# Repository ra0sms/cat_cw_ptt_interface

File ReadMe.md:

# CAT CW PTT AUDIO interface for a transceiver

More information - https://ra0sms.com/cat-cw-ptt-audio-interface/

------

------

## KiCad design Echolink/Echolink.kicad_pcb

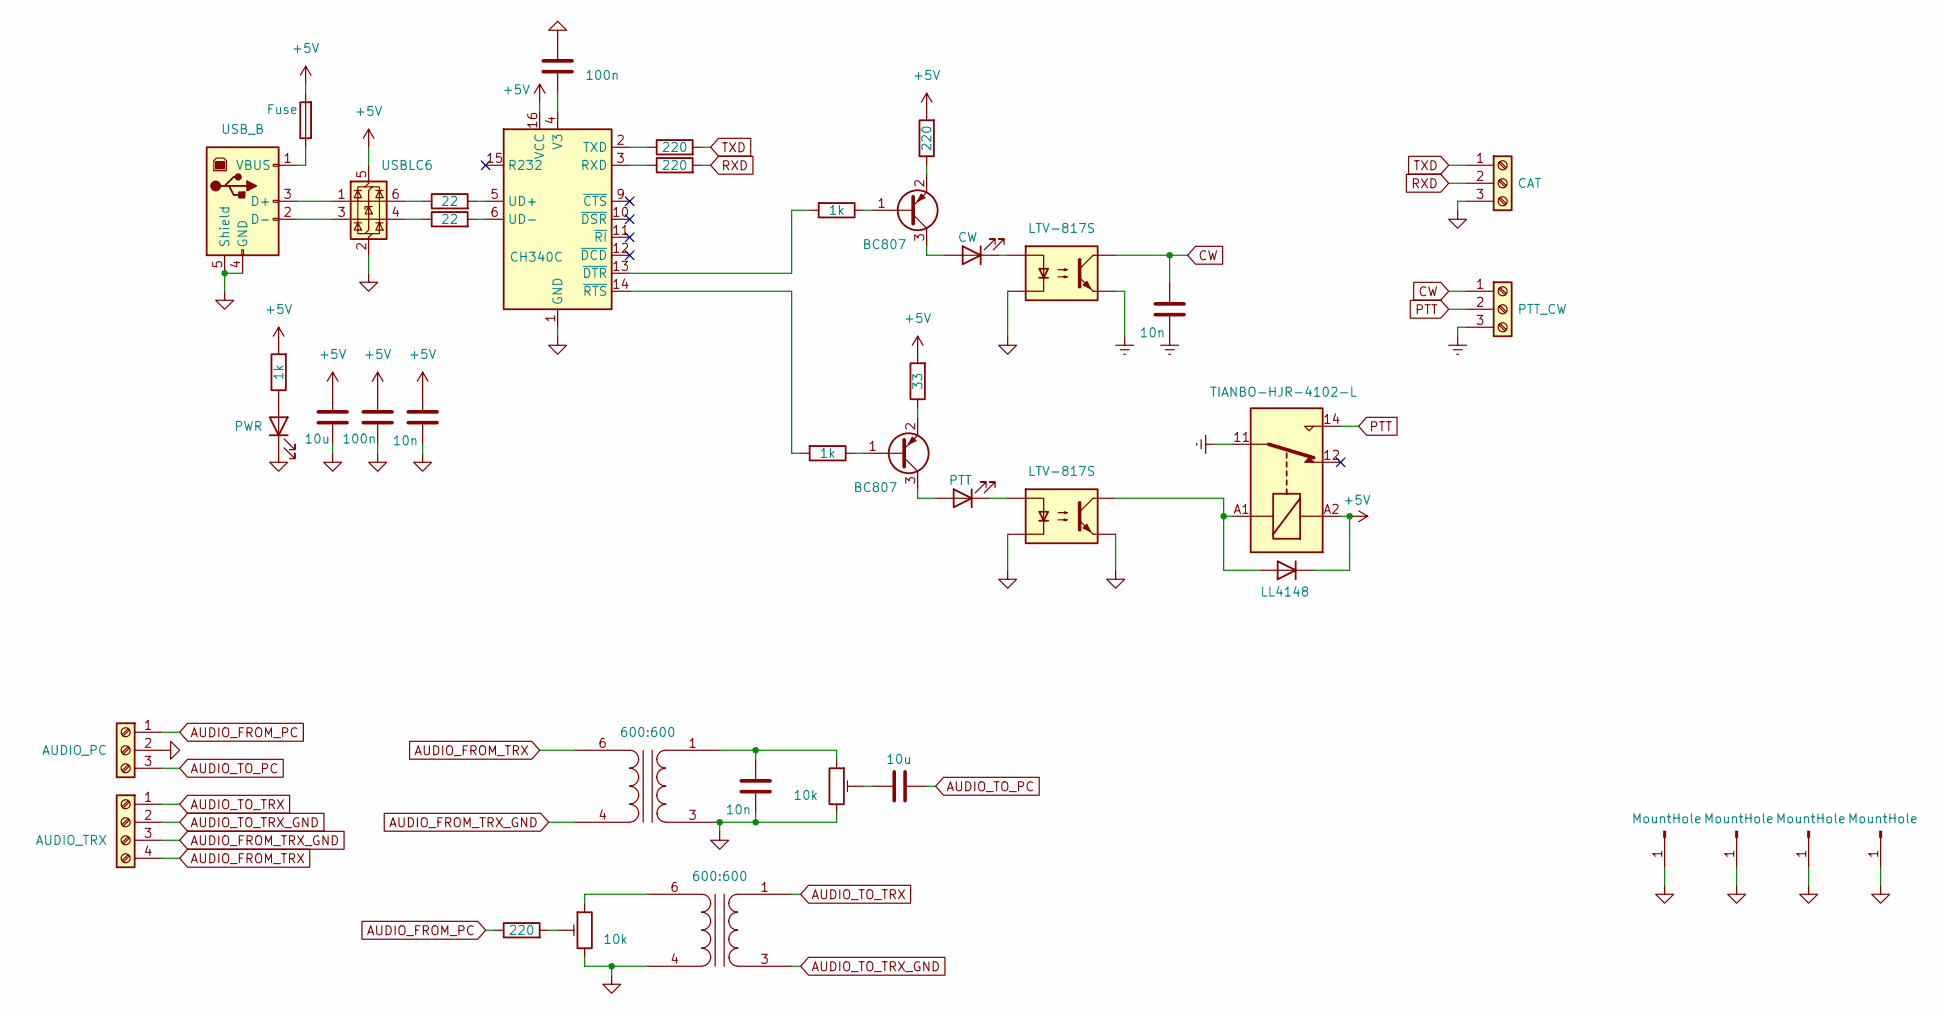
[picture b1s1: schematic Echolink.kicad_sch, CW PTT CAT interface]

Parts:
C1, C8: 10u; C_1206_3216Metric
C2, C3: 100n; C_1206_3216Metric
C4, C5, C7: 10n; C_1206_3216Metric
D1: PWR; LED_1206_3216Metric
D2: CW; LED_1206_3216Metric
D3: LL4148; D_MiniMELF
D4: PTT; LED_1206_3216Metric
F1: Fuse; R_1206_3216Metric
J1: USB_B; USB_B_OST_USB-B1HSxx_Horizontal
J2: AUDIO_PC; TerminalBlock_MetzConnect_Type055_RT01503HDWU_1x03_P5.00mm_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
J3: AUDIO_TRX; TerminalBlock_MetzConnect_Type055_RT01504HDWU_1x04_P5.00mm_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
J4, J7, J8, J9: MountHole; MountingHole_3.2mm_M3_DIN965_Pad
J5: CAT; TerminalBlock_MetzConnect_Type055_RT01503HDWU_1x03_P5.00mm_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
J6: PTT_CW; TerminalBlock_MetzConnect_Type055_RT01503HDWU_1x03_P5.00mm_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
K11: TIANBO-HJR-4102-L; Relay_SPDT_CUI_SR5
Q1, Q2: BC807; SOT-23
R1, R4, R7, R10: 220; R_1206_3216Metric
R2, R3: 22; R_1206_3216Metric
R5, R6, R8: 1k; R_1206_3216Metric
R9: 33; R_1206_3216Metric
RV1, RV2: 10k; Potentiometer_Bourns_3296W_Vertical
T1, T2: 600:600; Transformer_NF_ETAL_1-1_P1200
U1: CH340C; SOIC-16_3.9x9.9mm_P1.27mm
U2: USBLC6; SOT-23-6
U5, U6: LTV-817S; SMDIP-4_W9.53mm

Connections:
+5V: C1.1, C3.1, C4.1, D3.1 (K), F1.2, K11.A2, R5.2, R7.2, R9.2, U1.16 (VCC), U2.5 (VBUS)
AUDIO_FROM_PC: J2.1, R10.1
AUDIO_FROM_TRX: J3.4, T2.6 (AA)
AUDIO_FROM_TRX_GND: J3.3, T2.4 (AB)
AUDIO_TO_PC: C8.2, J2.3
AUDIO_TO_TRX: J3.1, T1.1 (SB)
AUDIO_TO_TRX_GND: J3.2, T1.3 (SA)
CW: C5.1, J6.1, U6.4
GND: C1.2, C2.1, C3.2, C4.2, C7.2, D1.1 (K), J1.4 (GND), J1.5 (Shield), J2.2, J4.1, J5.3, J7.1, J8.1, J9.1, RV1.3, RV2.3, T1.4 (AB), T2.3 (SA), U1.1 (GND), U2.2 (GND), U5.2, U5.3, U6.2
GNDREF: C5.2, J6.3, K11.11, U6.3
unnamed: C8.1, RV1.2
unnamed: D1.2 (A), R5.1
unnamed: D2.2 (A), Q1.3 (C)
unnamed: D2.1 (K), U6.1
unnamed: D3.2 (A), K11.A1, U5.4
unnamed: D4.2 (A), Q2.3 (C)
unnamed: D4.1 (K), U5.1
unnamed: J1.3 (D+), U2.1 (I/O1)
unnamed: J1.2 (D-), U2.3 (I/O2)
unnamed: F1.1, J1.1 (VBUS)
unnamed: Q1.1 (B), R6.1
unnamed: Q1.2 (E), R7.1
unnamed: Q2.1 (B), R8.1
unnamed: Q2.2 (E), R9.1
unnamed: R2.1, U2.6 (I/O1)
unnamed: R3.1, U2.4 (I/O2)
unnamed: R10.2, RV2.2
unnamed: RV2.1, T1.6 (AA)
unnamed: C7.1, RV1.1, T2.1 (SB)
unnamed: R4.1, U1.3 (RXD)
unnamed: R1.1, U1.2 (TXD)
unnamed: R2.2, U1.5 (UD+)
unnamed: R3.2, U1.6 (UD-)
unnamed: C2.2, U1.4 (V3)
unnamed: R6.2, U1.13 (~DTR)
unnamed: R8.2, U1.14 (~RTS)
PTT: J6.2, K11.14
RXD: J5.2, R4.2
TXD: J5.1, R1.2

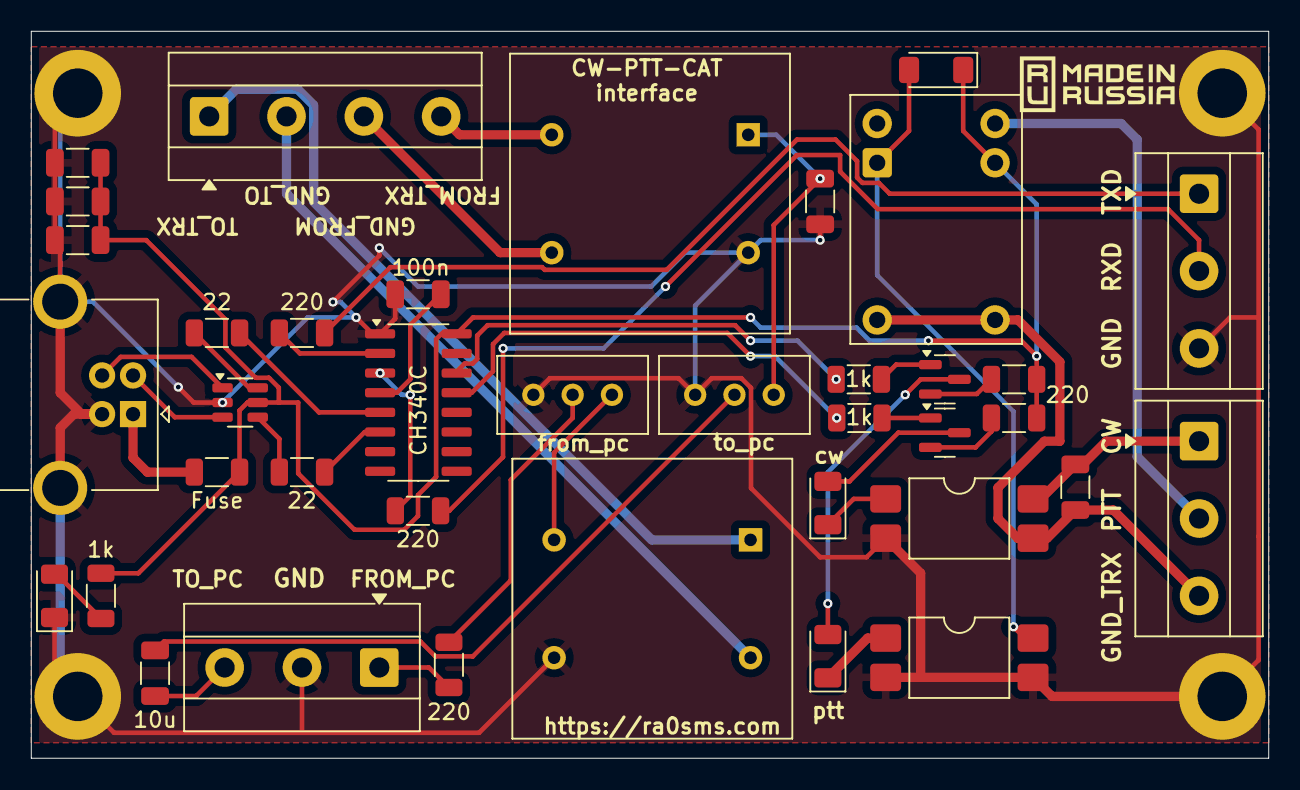
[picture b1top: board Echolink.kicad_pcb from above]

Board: 2 copper layers, 80.0 x 47.0 mm, 42 parts (0 on the bottom side), 39 nets.

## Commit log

2025-10-21 add pics
2026-03-26 change optotransistor, add some pics
